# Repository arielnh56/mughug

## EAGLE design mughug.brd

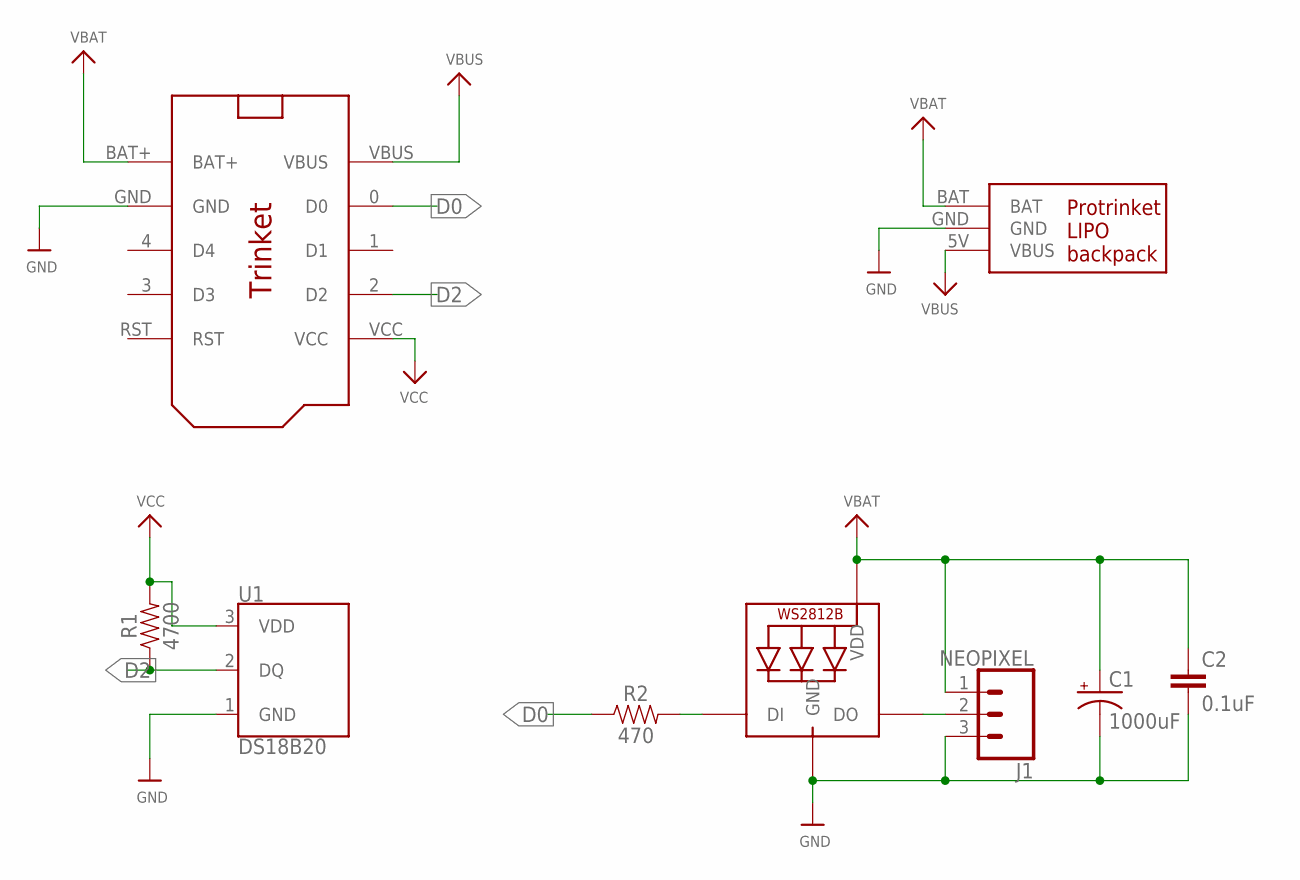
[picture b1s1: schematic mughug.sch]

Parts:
C1: 1000uF; 150CLZ-0810
C2: 0.1uF; 0603
J1: NEOPIXEL; 1X03
LED1: WS2812B5050; WS2812B
R1: 4700; 0603
R2: 470; 0603
U1: DS18B20; TO-92-AMMO
U$1: TRINKETNOHOLES; TRINKET_NOHOLES
U$2: PROTRINKETLIPO; PROTRINKETLIPO_NOHOLE

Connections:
D0: R2.1, U$1.0 (D0)
D2: R1.1, U1.2 (DQ), U$1.2 (D2)
GND: C1.-, C2.2, J1.3, LED1.3-GND (GND), U1.1 (GND), U$1.GND, U$2.GND
unnamed: LED1.4-DIN (DI), R2.2
unnamed: J1.2, LED1.2-DOUT (DO)
VBAT: C1.+, C2.1, J1.1, LED1.1-VDD (VDD), U$1.BAT+, U$2.BAT
VBUS: U$1.VBUS, U$2.5V (VBUS)
VCC: R1.2, U1.3 (VDD), U$1.VCC

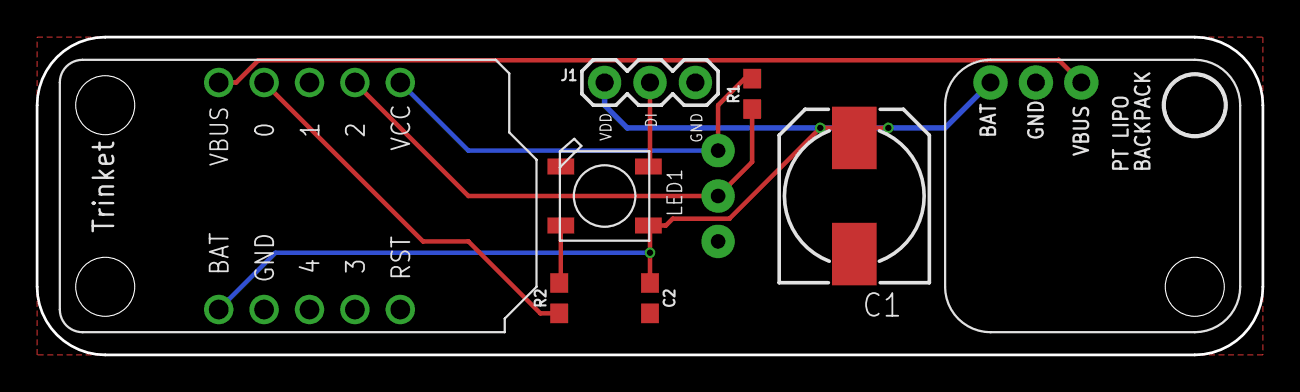
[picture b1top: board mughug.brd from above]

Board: 2 copper layers, 68.6 x 17.8 mm, 13 parts (1 on the bottom side), 8 nets.

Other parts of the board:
U$9, U$10, U$11, U$12: STAND-OFF

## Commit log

2018-01-28 commit design from 1/23/17 meeting
2018-01-30 Board reshuffle for oshpark
    Added thicker board outline
    moved neopixel to board center
    small passived aligned same direction
    12mil track for VBAT
    added silkscreen
    added corner holes for attachment
2018-01-30 Final tweak for oshpark proto order
    oshpark order dm4ze97u
2021-10-30 Check in source code from USB stick
    Checking in the source code from the USB drive in the project box
2021-10-30 Added board images
    Downloaded pcb board images from oshpark order history
2021-10-31 Create schematic1.pdf
    exported schematic to pdf

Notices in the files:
parts and their libraries:
SparkFun-Capacitors: Licensing: Creative Commons ShareAlike 4.0 International - https://creativecommons.org/licenses/by-sa/4.0
microbuilder: This work is placed in the public domain, and may be freely used for commercial and non-commercial work with the following conditions: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
